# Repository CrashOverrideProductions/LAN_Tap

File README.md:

# Lan Tap 

### Project: Passive Ethernet Tap 

<!-- Repo Cover Image -->

<!-- Repo Stats -->

### Details
This Lan Tap is essentially a clone of the Great Scott Gadgets, Throwing Star LAN Tap

##### SOURCE
<a href="http://greatscottgadgets.com/throwingstar/throwing-star-20110217.tar.gz"> Download </a> the open source design files (made with KiCad).
Read about the history of the Throwing Star LAN Tap.
The following instructions will help you assemble and use your Throwing Star LAN Tap. (<a href="http://greatscottgadgets.com/throwingstar/throwing-star-instructions.pdf">Download</a> these instructions for printing.)

### What is a Lan Tap?
The LAN Tap is a passive Ethernet tap, requiring no power for operation. There are active methods of tapping Ethernet connections (e.g., a mirror port on a switch), but none can beat passive taps for portability. To the target network, the LAN Tap looks just like a section of cable, but the wires in the cable extend to the monitoring ports in addition to connecting one target port to the other.

The monitoring ports (J3 and J4) are receive-only; they connect to the receive data lines on the monitoring station but do not connect to the station's transmit lines. This makes it impossible for the monitoring station to accidentally transmit data packets onto the target network.

The LAN Tap is designed to monitor 10BASET and 100BASETX networks. It is not possible for an unpowered tap to perform monitoring of 1000BASET (Gigabit Ethernet) networks, so the LAN Tap intentionally degrades the quality of 1000BASET target networks, forcing them to negotiate a lower speed (typically 100BASETX) that can be passively monitored. This is the purpose of the two capacitors (C1 and C2).

The LAN Tap degrades signal quality to some extent. Except as described above for Gigabit networks, this rarely causes problems on the target network. In situations where very long cables are in use, the signal degradation could reduce network performance. It is a good practice to use cables that are not any longer than necessary.

##### USAGE

Use Ethernet cables to connect the LAN Tap (J1 and J2) in line with a target network to be monitored.

Use Ethernet cables to connect one or both of the monitoring ports (J3 and J4) to ports on one or two monitoring stations. Each port monitors traffic in one direction only.

Use your favorite software (e.g., tcpdump or Wireshark) on the monitoring station(s) to capture network traffic.

---
<!-- To Do List -->
### To Do List
- [x] Complete Readme.md
- [x] Design Schematic
- [x] Design Board
- [ ] Order Prototype PCBs
- [ ] Design 3D Print Shell
- [ ] Research Injection Moulded Shell

---
### PCB Design

##### BOM

| Part#       | Part                                                        | Mouser Part#       | Qty | Price   | Total   |
| ----------- | ----------------------------------------------------------- | ------------------ | :-: | :-----: | ------: |
| J1,J2,J3,J4 | Modular Connectors / Ethernet Connectors RJ45 Connector     | SS-6488-FLS        | 4   | $1.24   | $4.96   |
| C1,C2       | Multilayer Ceramic Capacitor - Leaded 220pF 50volts 5%      | 594-K221J15C0GF5UH5| 2   | $0.135  | $0.27   |
|             |                                                             | TOTAL AUD          |     |         | $5.23   |

<!-- Licencing Always at the Bottom -->
------------
### Licencing 

**CERN-Open Hardware Licence - Permissive**

```
CERN Open Hardware Licence Version 2 - Permissive

Preamble

CERN has developed this licence to promote collaboration among
hardware designers and to provide a legal tool which supports the
freedom to use, study, modify, share and distribute hardware designs
and products based on those designs. Version 2 of the CERN Open
Hardware Licence comes in three variants: this licence, CERN-OHL-P
(permissive); and two reciprocal licences: CERN- OHL-W (weakly
reciprocal) and CERN-OHL-S (strongly reciprocal).

The CERN-OHL-P is copyright CERN 2020. Anyone is welcome to use it, in
unmodified form only.

Use of this Licence does not imply any endorsement by CERN of any
Licensor or their designs nor does it imply any involvement by CERN in
their development.

1 Definitions

  1.1 'Licence' means this CERN-OHL-P.

  1.2 'Source' means information such as design materials or digital
      code which can be applied to Make or test a Product or to
      prepare a Product for use, Conveyance or sale, regardless of its
      medium or how it is expressed. It may include Notices.

  1.3 'Covered Source' means Source that is explicitly made available
      under this Licence.

  1.4 'Product' means any device, component, work or physical object,
      whether in finished or intermediate form, arising from the use,
      application or processing of Covered Source.

  1.5 'Make' means to create or configure something, whether by
     manufacture, assembly, compiling, loading or applying Covered
     Source or another Product or otherwise.

  1.6 'Notice' means copyright, acknowledgement and trademark notices,
      references to the location of any Notices, modification notices
      (subsection 3.3(b)) and all notices that refer to this Licence
      and to the disclaimer of warranties that are included in the
      Covered Source.

  1.7 'Licensee' or 'You' means any person exercising rights under
      this Licence.

  1.8 'Licensor' means a person who creates Source or modifies Covered
      Source and subsequently Conveys the resulting Covered Source
      under the terms and conditions of this Licence. A person may be
      a Licensee and a Licensor at the same time.

  1.9 'Convey' means to communicate to the public or distribute.

2 Applicability

  2.1 This Licence governs the use, copying, modification, Conveying
      of Covered Source and Products, and the Making of Products. By
      exercising any right granted under this Licence, You irrevocably
      accept these terms and conditions.

  2.2 This Licence is granted by the Licensor directly to You, and
      shall apply worldwide and without limitation in time.

  2.3 You shall not attempt to restrict by contract or otherwise the
      rights granted under this Licence to other Licensees.

  2.4 This Licence is not intended to restrict fair use, fair dealing,
      or any other similar right.

3 Copying, modifying and Conveying Covered Source

  3.1 You may copy and Convey verbatim copies of Covered Source, in
      any medium, provided You retain all Notices.

  3.2 You may modify Covered Source, other than Notices.

      You may only delete Notices if they are no longer applicable to
      the corresponding Covered Source as modified by You and You may
      add additional Notices applicable to Your modifications.

  3.3 You may Convey modified Covered Source (with the effect that You
      shall also become a Licensor) provided that You:

       a) retain Notices as required in subsection 3.2; and

       b) add a Notice to the modified Covered Source stating that You
          have modified it, with the date and brief description of how
          You have modified it.

  3.4 You may Convey Covered Source or modified Covered Source under
      licence terms which differ from the terms of this Licence
      provided that:

       a) You comply at all times with subsection 3.3; and

       b) You provide a copy of this Licence to anyone to whom You
          Convey Covered Source or modified Covered Source.

4 Making and Conveying Products

You may Make Products, and/or Convey them, provided that You ensure
that the recipient of the Product has access to any Notices applicable
to the Product.

5 DISCLAIMER AND LIABILITY

  5.1 DISCLAIMER OF WARRANTY -- The Covered Source and any Products
      are provided 'as is' and any express or implied warranties,
      including, but not limited to, implied warranties of
      merchantability, of satisfactory quality, non-infringement of
      third party rights, and fitness for a particular purpose or use
      are disclaimed in respect of any Source or Product to the
      maximum extent permitted by law. The Licensor makes no
      representation that any Source or Product does not or will not
      infringe any patent, copyright, trade secret or other
      proprietary right. The entire risk as to the use, quality, and
      performance of any Source or Product shall be with You and not
      the Licensor. This disclaimer of warranty is an essential part
      of this Licence and a condition for the grant of any rights
      granted under this Licence.

  5.2 EXCLUSION AND LIMITATION OF LIABILITY -- The Licensor shall, to
      the maximum extent permitted by law, have no liability for
      direct, indirect, special, incidental, consequential, exemplary,
      punitive or other damages of any character including, without
      limitation, procurement of substitute goods or services, loss of
      use, data or profits, or business interruption, however caused
      and on any theory of contract, warranty, tort (including
      negligence), product liability or otherwise, arising in any way
      in relation to the Covered Source, modified Covered Source
      and/or the Making or Conveyance of a Product, even if advised of
      the possibility of such damages, and You shall hold the
      Licensor(s) free and harmless from any liability, costs,
      damages, fees and expenses, including claims by third parties,
      in relation to such use.

6 Patents

  6.1 Subject to the terms and conditions of this Licence, each
      Licensor hereby grants to You a perpetual, worldwide,
      non-exclusive, no-charge, royalty-free, irrevocable (except as
      stated in this section 6, or where terminated by the Licensor
      for cause) patent license to Make, have Made, use, offer to
      sell, sell, import, and otherwise transfer the Covered Source
      and Products, where such licence applies only to those patent
      claims licensable by such Licensor that are necessarily
      infringed by exercising rights under the Covered Source as
      Conveyed by that Licensor.

  6.2 If You institute patent litigation against any entity (including
      a cross-claim or counterclaim in a lawsuit) alleging that the
      Covered Source or a Product constitutes direct or contributory
      patent infringement, or You seek any declaration that a patent
      licensed to You under this Licence is invalid or unenforceable
      then any rights granted to You under this Licence shall
      terminate as of the date such process is initiated.

7 General

  7.1 If any provisions of this Licence are or subsequently become
      invalid or unenforceable for any reason, the remaining
      provisions shall remain effective.

  7.2 You shall not use any of the name (including acronyms and
      abbreviations), image, or logo by which the Licensor or CERN is
      known, except where needed to comply with section 3, or where
      the use is otherwise allowed by law. Any such permitted use
      shall be factual and shall not be made so as to suggest any kind
      of endorsement or implication of involvement by the Licensor or
      its personnel.

  7.3 CERN may publish updated versions and variants of this Licence
      which it considers to be in the spirit of this version, but may
      differ in detail to address new problems or concerns. New
      versions will be published with a unique version number and a
      variant identifier specifying the variant. If the Licensor has
      specified that a given variant applies to the Covered Source
      without specifying a version, You may treat that Covered Source
      as being released under any version of the CERN-OHL with that
      variant. If no variant is specified, the Covered Source shall be
      treated as being released under CERN-OHL-S. The Licensor may
      also specify that the Covered Source is subject to a specific
      version of the CERN-OHL or any later version in which case You
      may apply this or any later version of CERN-OHL with the same
      variant identifier published by CERN.

  7.4 This Licence shall not be enforceable except by a Licensor
      acting as such, and third party beneficiary rights are
      specifically excluded.
```

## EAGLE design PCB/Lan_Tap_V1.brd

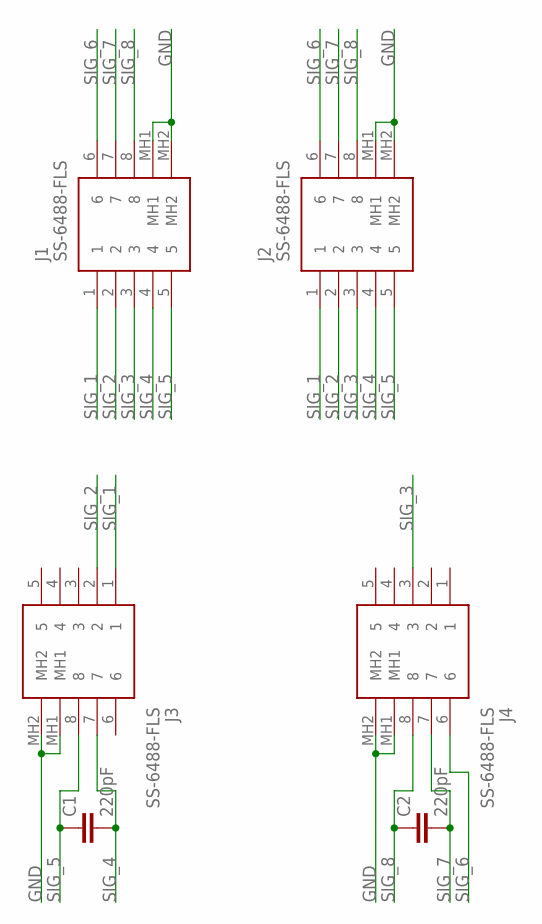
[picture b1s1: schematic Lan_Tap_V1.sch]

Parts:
C1, C2: 220pF; C2.5-2
J1, J2, J3, J4: SS-6488-FLS; SS6488FLS

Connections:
GND: J1.MH1, J1.MH2, J2.MH1, J2.MH2, J3.MH1, J3.MH2, J4.MH1, J4.MH2
SIG_1: J1.1, J2.1, J3.1
SIG_2: J1.2, J2.2, J3.2
SIG_3: J1.3, J2.3, J4.3
SIG_4: C1.2, J1.4, J2.4, J3.7
SIG_5: C1.1, J1.5, J2.5, J3.8
SIG_6: J1.6, J2.6, J4.6
SIG_7: C2.2, J1.7, J2.7, J4.7
SIG_8: C2.1, J1.8, J2.8, J4.8

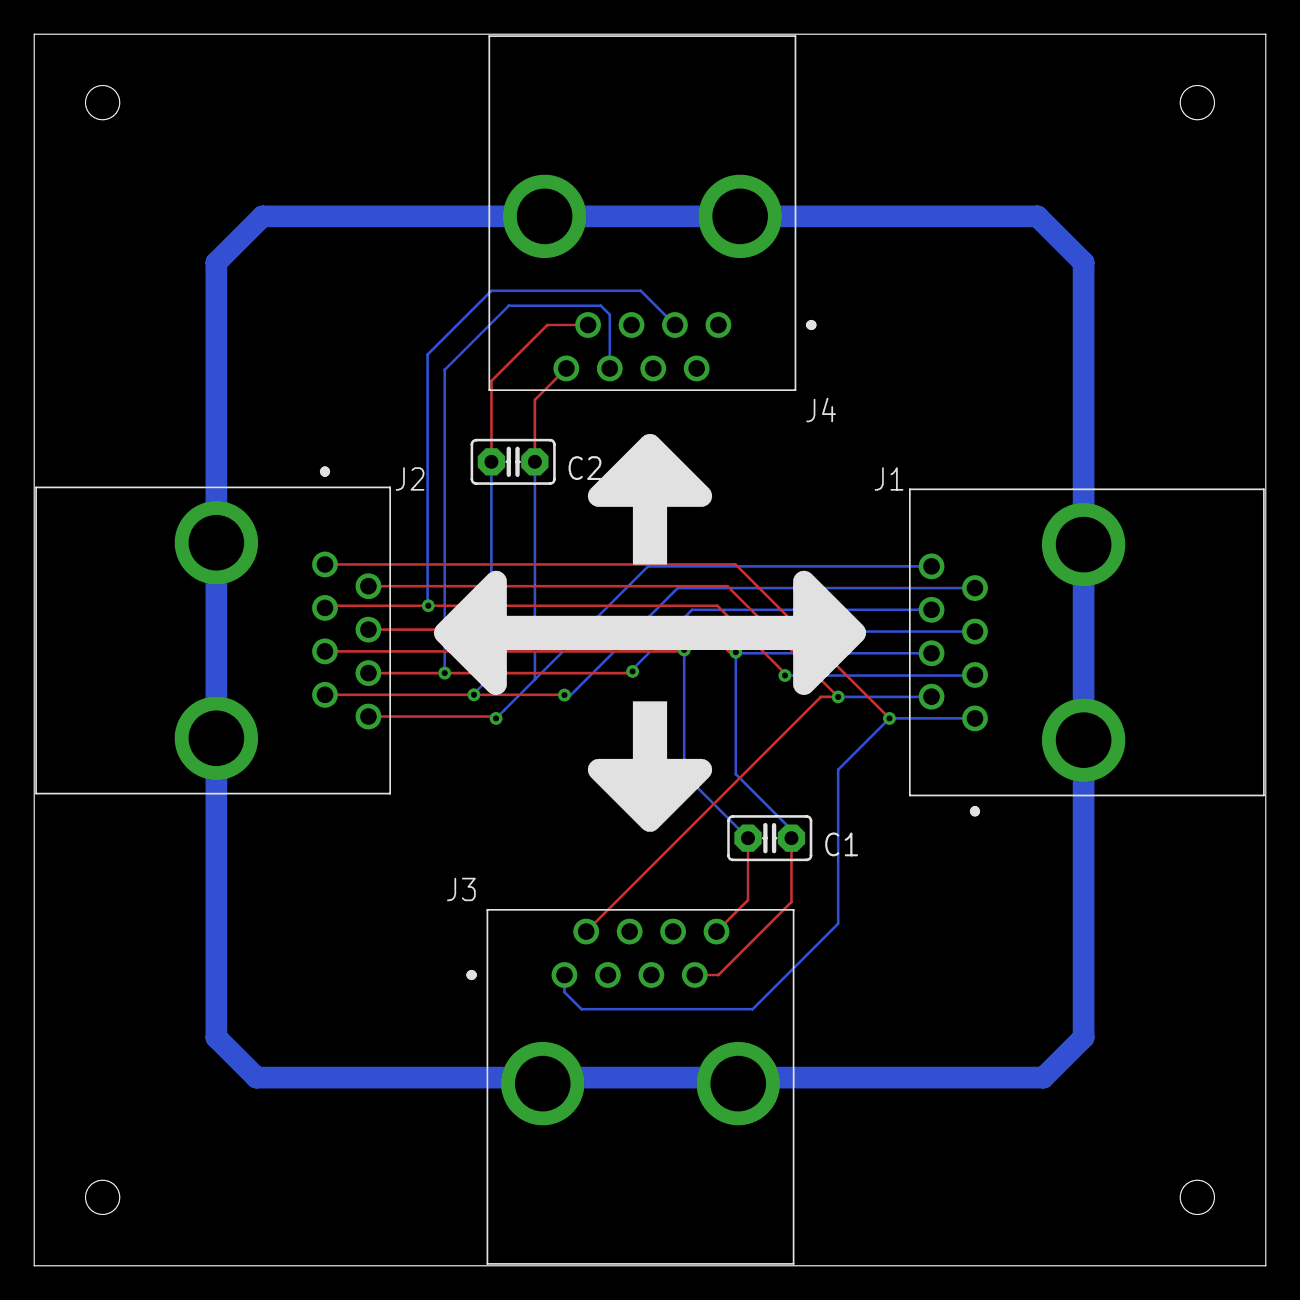
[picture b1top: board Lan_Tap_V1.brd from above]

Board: 2 copper layers, 72.0 x 72.0 mm, 6 parts (0 on the bottom side), 9 nets.

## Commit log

2021-06-28 Create Repo

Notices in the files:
README.md:
License: CERN OHL P
